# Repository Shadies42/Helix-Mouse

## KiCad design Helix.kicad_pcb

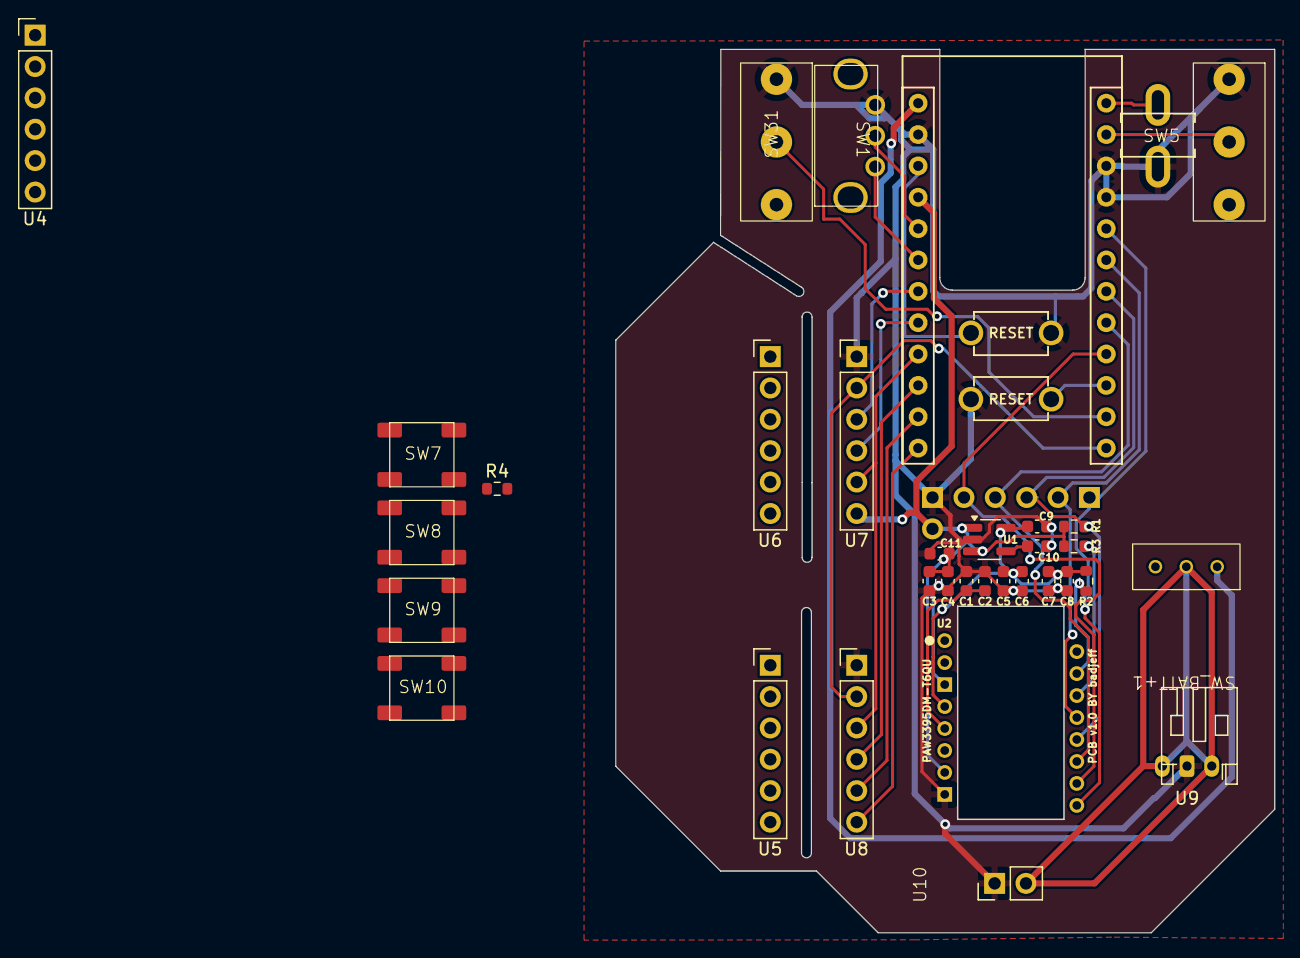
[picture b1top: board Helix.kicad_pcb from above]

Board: 2 copper layers, 53.4 x 71.6 mm, 38 parts (0 on the bottom side), 34 nets.

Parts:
C1: 4.7uF; C_0603_1608Metric
C2, C4, C5: 100nF; C_0603_1608Metric
C3, C6, C8: 10uF; C_0603_1608Metric
C7: 22uF; C_0603_1608Metric
C9, C11: 1uF; C_0603_1608Metric
C10: 22nF; C_0603_1608Metric
J1: Conn_01x02; PinHeader_1x02_P2.54mm_Vertical
J2: Conn_01x05; PinHeader_1x05_P2.54mm_Vertical
R1, R4: 10K; R_0603_1608Metric
R2: 4.7; R_0603_1608Metric
R3: 2M; R_0603_1608Metric
SW1, SW2: SW; GM 8.0
SW3, SW4: SW; TACT_SWITCH_TVBP06
SW5: SW; Scroll Button
SW7, SW8, SW9, SW10: SW; SPST Momentary SMD 1.6mm
SW31: Rotary_Encoder_Switch; MouseEncoder
SW_BATT+1: SW_SPST; 3pinBatt
U1: TLV74318PDBVR; SOT-23-5_HandSoldering
U2: PAW3395
U3: ProMicro; ProMicroSingleSide
U4, U5, U6, U7, U8: Pogo_2.54mm_6p
U9: JST_PH_S2B-PH-K_1x02_P2.00mm_DoubleSided
U10: Pogo_2.54_2p

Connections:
+1V8: C5.1, C6.1, C7.1, C8.1, C9.1, R2.1, U1.5 (OUT), U2.4 (VDD)
AnaA: U3.18 (A1(PF6)), U7.3
AnaB: U3.17 (A0(PF7)), U7.4
DPI: SW3.2, U3.10 (D7(PE6))
EncA: SW31.B, U3.20 (A3(PF4))
EncB: SW31.A, U3.19 (A2(PF5))
Ext1: U3.16 (D15(PB1)), U7.5, U8.3
Ext2: U3.15 (D14(PB3)), U8.4
Ext3: U3.14 (D16(PB2)), U8.5
Ext4: U3.13 (D10(PB6)), U8.6
GND: C1.2, C2.2, C3.2, C4.2, C5.2, C6.2, C7.2, C8.2, C9.2, C10.2, C11.2, J1.1, SW1.1, SW2.1, SW3.1, SW4.1, SW5.1, SW31.C, U1.2 (GND), U2.3 (GND), U2.8 (GNDIO), U3.3 (GND), U3.4 (GND), U3.23 (GND), U7.1, U8.1, U9.1, U10.1
IND: U3.12 (D9(PB5)), U7.2, U8.2
Left: SW1.2, U3.11 (D8(PB4))
MISO: J2.3, R1.2, U2.12 (MISO), U3.7 (D4(PD4))
MOSI: J2.4, U2.11 (MOSI), U3.8 (D5(PC6))
MOTION: J2.1, U2.9 (MOTION), U3.5 (SDA(PD1))
Middle: SW5.2, U3.1 (TX(PD3))
unnamed: SW_BATT+1.1 (A), U3.24 (RAW)
unnamed: SW_BATT+1.2 (B), U9.2, U10.2
unnamed: C10.1, U1.4 (NC)
unnamed: R2.2, U2.15 (LED_P)
unnamed: R3.2, U2.14 (NRESET)
unnamed: C1.1, C2.1, U2.5 (VDDREG)
unnamed: R4.2, SW7.2, SW8.2, SW9.2, SW10.2, U5.1
unnamed: R4.1, U5.2
unnamed: SW7.1, U5.3
unnamed: SW8.1, U5.4
unnamed: SW9.1, U5.5
unnamed: SW10.1, U5.6
RST: SW4.2, U3.22 (RST)
Right: SW2.2, U3.2 (RX(PD2))
SCLK: J2.5, U2.10 (SCLK), U3.9 (D6(PD7))
VIN: C3.1, C4.1, C11.1, J1.2, R1.1, R3.1, U1.1 (IN), U1.3 (EN), U2.7 (VDDIO), U3.21 (VCC), U7.6
nCS: J2.2, U2.13 (NCS), U3.6 (SCL(PD0))
